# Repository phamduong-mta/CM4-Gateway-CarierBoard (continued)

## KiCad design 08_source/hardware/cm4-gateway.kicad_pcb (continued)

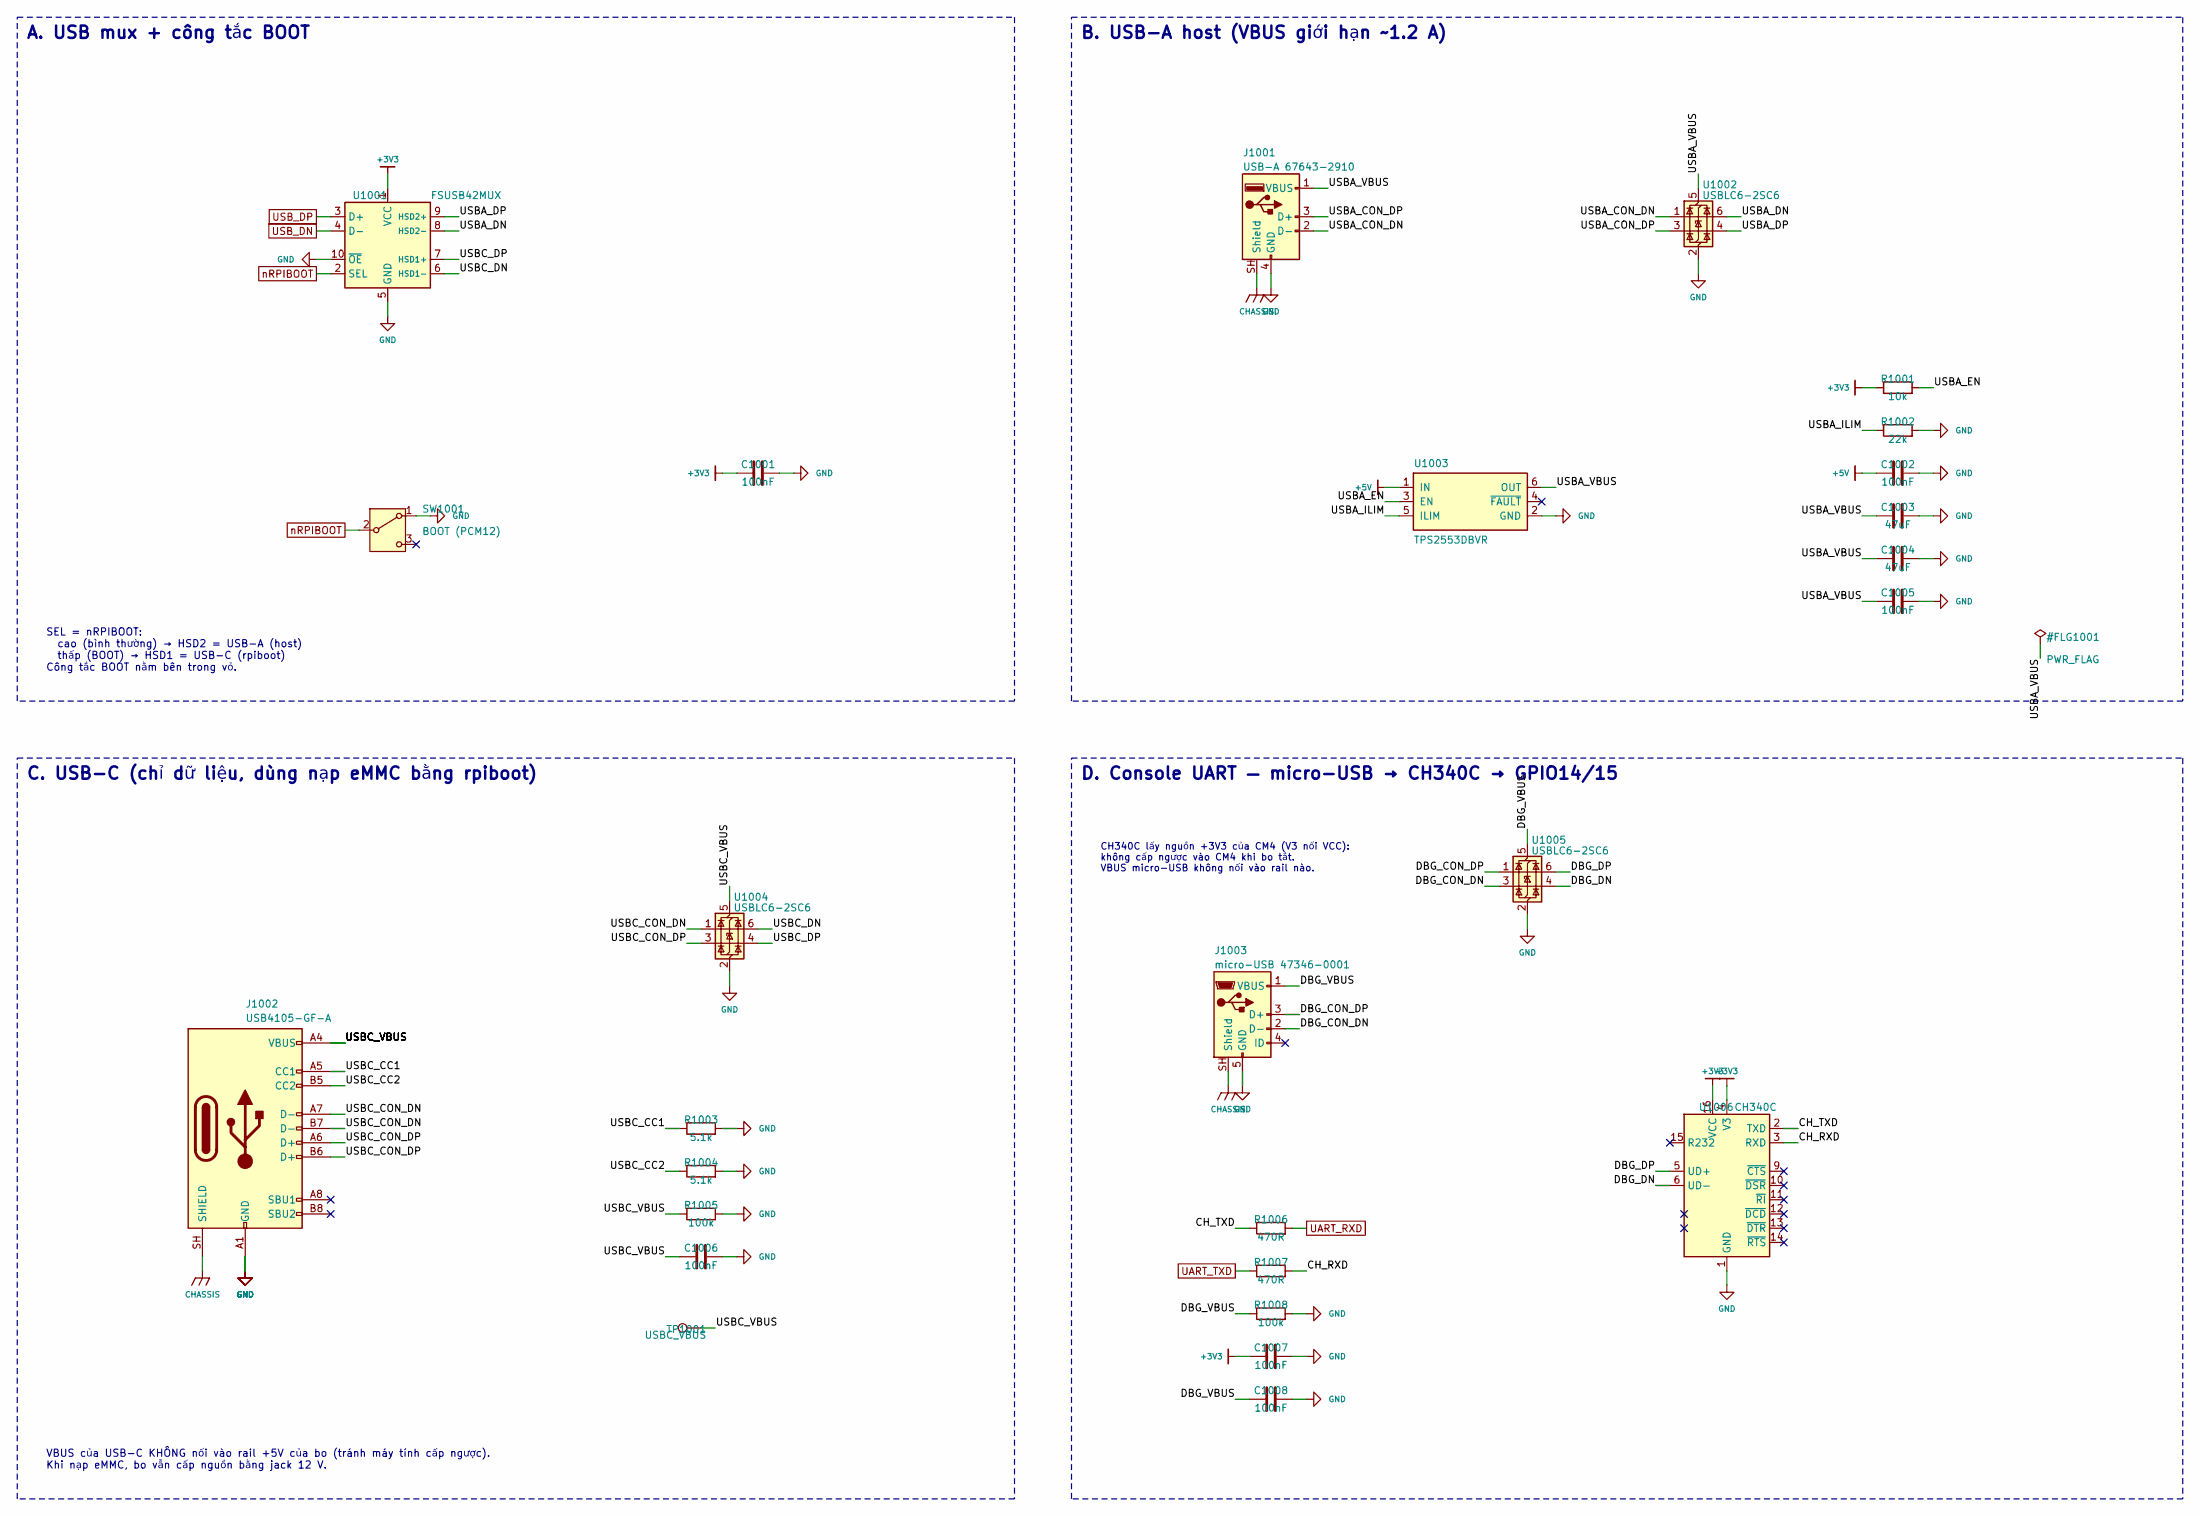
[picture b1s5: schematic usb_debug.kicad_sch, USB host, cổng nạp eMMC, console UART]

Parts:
C1001, C1002, C1005, C1006, C1007, C1008: 100nF; C_0402_1005Metric; MPN CL05B104KO5NNNC; LCSC C1525
C1003, C1004: 47uF; C_1206_3216Metric; MPN CL31A476MPHNNNE; LCSC C96123
J1001: USB-A 67643-2910; USB_A_Molex_67643_Horizontal; MPN 67643-2910; LCSC C564920
J1002: USB4105-GF-A; USB_C_Receptacle_GCT_USB4105-xx-A_16P_TopMnt_Horizontal; MPN USB4105-GF-A; LCSC C3020560
J1003: micro-USB 47346-0001; USB_Micro-B_Molex_47346-0001; MPN 47346-0001; LCSC C132560
R1001: 10k; R_0402_1005Metric; MPN 0402WGF1002TCE; LCSC C25744
R1002: 22k; R_0402_1005Metric; MPN 0402WGF2202TCE; LCSC C25768
R1003, R1004: 5.1k; R_0402_1005Metric; MPN 0402WGF5101TCE; LCSC C25905
R1005, R1008: 100k; R_0402_1005Metric; MPN 0402WGF1003TCE; LCSC C25741
R1006, R1007: 470R; R_0402_1005Metric; MPN 0402WGF4700TCE; LCSC C25117
SW1001: BOOT (PCM12); SW_SPDT_PCM12; MPN PCM12SMTR; LCSC C221841
TP1001: USBC_VBUS; TestPoint_Pad_D1.0mm
U1001: FSUSB42MUX; MSOP-10_3x3mm_P0.5mm; MPN FSUSB42MUX; LCSC C11355
U1002, U1004, U1005: USBLC6-2SC6; SOT-23-6; MPN USBLC6-2SC6; LCSC C7519
U1003: TPS2553DBVR; SOT-23-6; MPN TPS2553DBVR; LCSC C55266
U1006: CH340C; SOIC-16_3.9x9.9mm_P1.27mm; MPN CH340C; LCSC C84681

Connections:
+3V3: C1001.1, C1007.1, R1001.1, U1001.1 (VCC), U1006.4 (V3), U1006.16 (VCC); also elsewhere on the board
+5V: C1002.1, U1003.1 (IN); also elsewhere on the board
/USB_Debug/CH_RXD: R1007.2, U1006.3 (RXD)
/USB_Debug/CH_TXD: R1006.1, U1006.2 (TXD)
/USB_Debug/DBG_CON_DN: J1003.2 (D-), U1005.3 (I/O2)
/USB_Debug/DBG_CON_DP: J1003.3 (D+), U1005.1 (I/O1)
/USB_Debug/DBG_DN: U1005.4 (I/O2), U1006.6 (UD-)
/USB_Debug/DBG_DP: U1005.6 (I/O1), U1006.5 (UD+)
/USB_Debug/DBG_VBUS: C1008.1, J1003.1 (VBUS), R1008.1, U1005.5 (VBUS)
/USB_Debug/USBA_CON_DN: J1001.2 (D-), U1002.1 (I/O1)
/USB_Debug/USBA_CON_DP: J1001.3 (D+), U1002.3 (I/O2)
/USB_Debug/USBA_DN: U1001.8 (HSD2-), U1002.6 (I/O1)
/USB_Debug/USBA_DP: U1001.9 (HSD2+), U1002.4 (I/O2)
/USB_Debug/USBA_EN: R1001.2, U1003.3 (EN)
/USB_Debug/USBA_ILIM: R1002.1, U1003.5 (ILIM)
/USB_Debug/USBA_VBUS: C1003.1, C1004.1, C1005.1, J1001.1 (VBUS), U1002.5 (VBUS), U1003.6 (OUT)
/USB_Debug/USBC_CC1: J1002.A5 (CC1), R1003.1
/USB_Debug/USBC_CC2: J1002.B5 (CC2), R1004.1
/USB_Debug/USBC_CON_DN: J1002.A7 (D-), J1002.B7 (D-), U1004.1 (I/O1)
/USB_Debug/USBC_CON_DP: J1002.A6 (D+), J1002.B6 (D+), U1004.3 (I/O2)
/USB_Debug/USBC_DN: U1001.6 (HSD1-), U1004.6 (I/O1)
/USB_Debug/USBC_DP: U1001.7 (HSD1+), U1004.4 (I/O2)
/USB_Debug/USBC_VBUS: C1006.1, J1002.A4 (VBUS), J1002.A9 (VBUS), J1002.B4 (VBUS), J1002.B9 (VBUS), R1005.1, TP1001.1, U1004.5 (VBUS)
CHASSIS: J1001.SH (Shield), J1002.SH (SHIELD), J1003.SH (Shield); also elsewhere on the board
GND: C1001.2, C1002.2, C1003.2, C1004.2, C1005.2, C1006.2, C1007.2, C1008.2, J1001.4 (GND), J1002.A1 (GND), J1002.A12 (GND), J1002.B1 (GND), J1002.B12 (GND), J1003.5 (GND), R1002.2, R1003.2, R1004.2, R1005.2, R1008.2, SW1001.1 (A), U1001.5 (GND), U1001.10 (~OE), U1002.2 (GND), U1003.2 (GND), U1004.2 (GND), U1005.2 (GND), U1006.1 (GND); also elsewhere on the board
UART_RXD: R1006.2; also elsewhere on the board
UART_TXD: R1007.1; also elsewhere on the board
USB_DN: U1001.4 (D-); also elsewhere on the board
USB_DP: U1001.3 (D+); also elsewhere on the board
nRPIBOOT: SW1001.2 (B), U1001.2 (SEL); also elsewhere on the board

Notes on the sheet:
A. USB mux + công tắc BOOT
SEL = nRPIBOOT: cao (bình thường) → HSD2 = USB-A (host) thấp (BOOT) → HSD1 = USB-C (rpiboot) Công tắc BOOT nằm bên trong vỏ.
B. USB-A host (VBUS giới hạn ~1.2 A)
C. USB-C (chỉ dữ liệu, dùng nạp eMMC bằng rpiboot)
VBUS của USB-C KHÔNG nối vào rail +5V của bo (tránh máy tính cấp ngược). Khi nạp eMMC, bo vẫn cấp nguồn bằng jack 12 V.
D. Console UART — micro-USB → CH340C → GPIO14/15
CH340C lấy nguồn +3V3 của CM4 (V3 nối VCC): không cấp ngược vào CM4 khi bo tắt. VBUS micro-USB không nối vào rail nào.

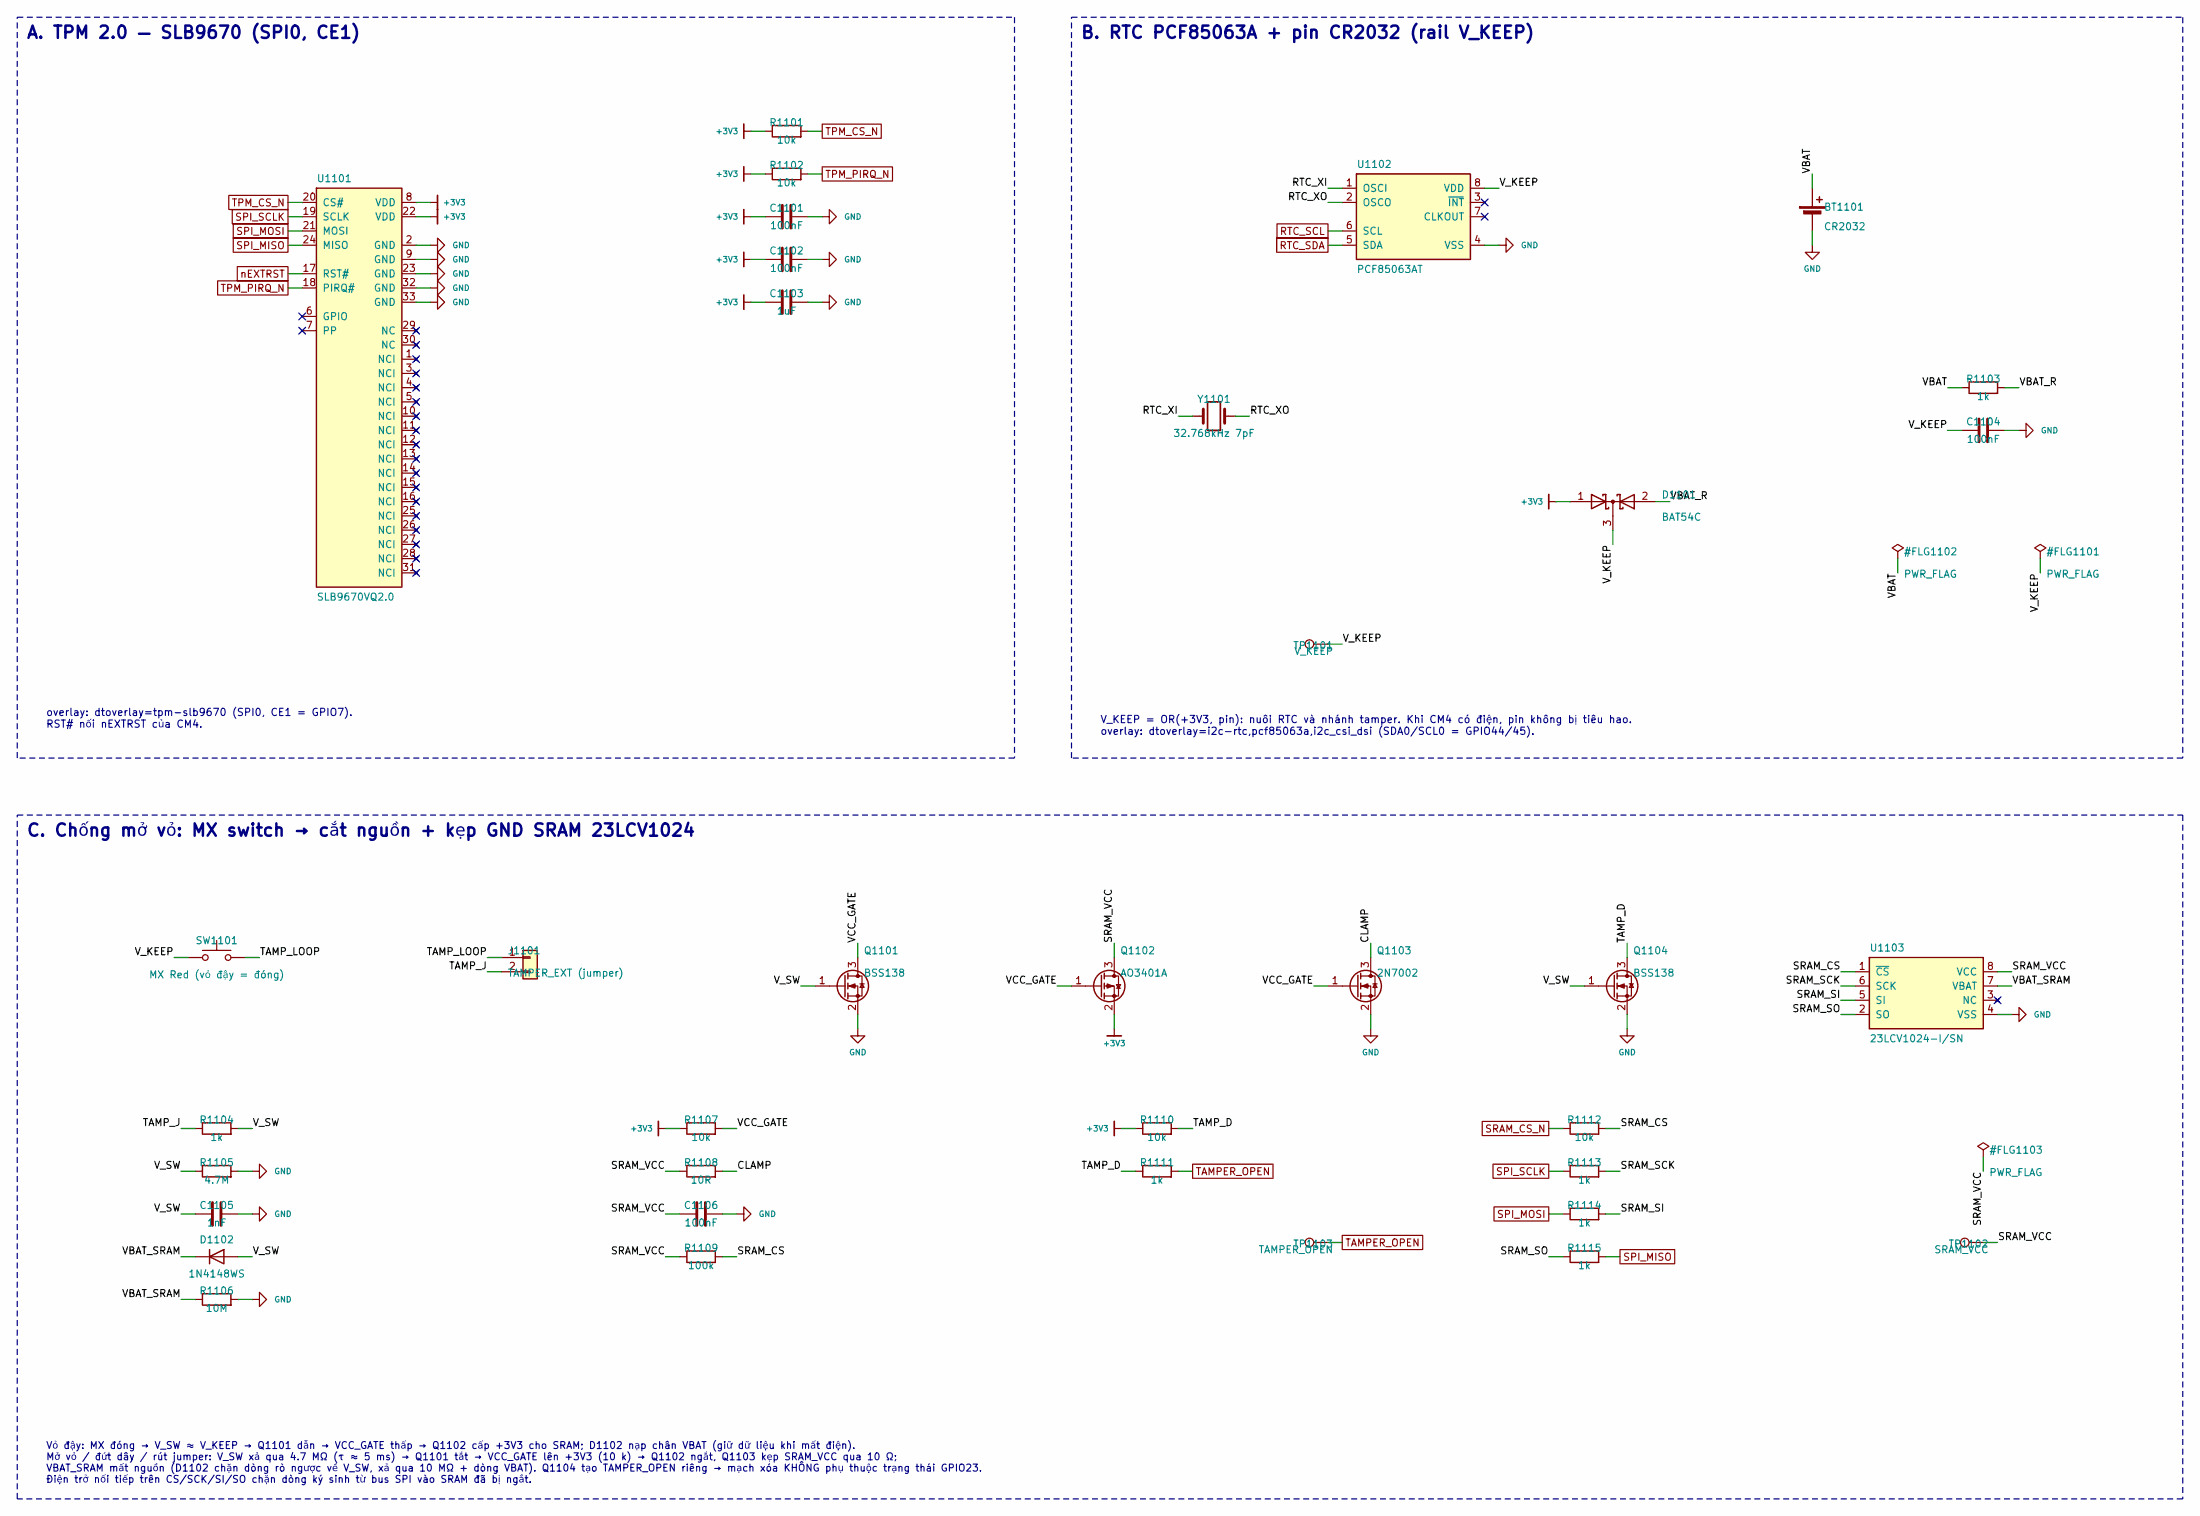
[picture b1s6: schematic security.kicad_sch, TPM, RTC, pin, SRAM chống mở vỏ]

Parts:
BT1101: CR2032; BatteryHolder_Keystone_3034_1x20mm; MPN 3034; LCSC C5199422
C1101, C1102, C1104, C1106: 100nF; C_0402_1005Metric; MPN CL05B104KO5NNNC; LCSC C1525
C1103: 1uF; C_0402_1005Metric; MPN CL05A105KA5NQNC; LCSC C52923
C1105: 1nF; C_0402_1005Metric; MPN CL05B102KB5NNNC; LCSC C14442
D1101: BAT54C; SOT-23; MPN BAT54C; LCSC C2135
D1102: 1N4148WS; D_SOD-323; MPN 1N4148WS; LCSC C2128
J1101: TAMPER_EXT (jumper); PinHeader_1x02_P2.54mm_Vertical; MPN B-2100S02P-A110; LCSC C124375
Q1101, Q1104: BSS138; SOT-23; MPN LBSS138LT1G; LCSC C8490
Q1102: AO3401A; SOT-23; MPN AO3401A; LCSC C15127
Q1103: 2N7002; SOT-23; MPN 2N7002; LCSC C8545
R1101, R1102, R1107, R1110, R1112: 10k; R_0402_1005Metric; MPN 0402WGF1002TCE; LCSC C25744
R1103, R1104, R1111, R1113, R1114, R1115: 1k; R_0402_1005Metric; MPN 0402WGF1001TCE; LCSC C11702
R1105: 4.7M; R_0402_1005Metric; MPN 0402WGF4704TCE; LCSC C474132
R1106: 10M; R_0402_1005Metric; MPN 0402WGF1005TCE; LCSC C26082
R1108: 10R; R_0402_1005Metric; MPN 0402WGF100JTCE; LCSC C25077
R1109: 100k; R_0402_1005Metric; MPN 0402WGF1003TCE; LCSC C25741
SW1101: MX Red (vỏ đậy = đóng); SW_Cherry_MX_1.00u_PCB; MPN CPG151101D05; LCSC C49234236
TP1101: V_KEEP; TestPoint_Pad_D1.0mm
TP1102: SRAM_VCC; TestPoint_Pad_D1.0mm
TP1103: TAMPER_OPEN; TestPoint_Pad_D1.0mm
U1101: SLB9670VQ2.0; QFN-32-1EP_5x5mm_P0.5mm_EP3.6x3.6mm; MPN SLB9670VQ20FW785XTMA1; LCSC C1012863
U1102: PCF85063AT; SOIC-8_3.9x4.9mm_P1.27mm; MPN PCF85063AT/AY; LCSC C5151540
U1103: 23LCV1024-I/SN; SOIC-8_3.9x4.9mm_P1.27mm; MPN 23LCV1024-I/SN; LCSC C615097
Y1101: 32.768kHz 7pF; Crystal_SMD_3215-2Pin_3.2x1.5mm; MPN SC-32S 32.768kHz 7pF; LCSC C97604

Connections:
+3V3: C1101.1, C1102.1, C1103.1, D1101.1 (A), Q1102.2 (S), R1101.1, R1102.1, R1107.1, R1110.1, U1101.8 (VDD), U1101.22 (VDD); also elsewhere on the board
/Security/CLAMP: Q1103.3 (D), R1108.2
/Security/RTC_XI: U1102.1 (OSCI), Y1101.1
/Security/RTC_XO: U1102.2 (OSCO), Y1101.2
/Security/SRAM_CS: R1109.2, R1112.2, U1103.1 (~CS)
/Security/SRAM_SCK: R1113.2, U1103.6 (SCK)
/Security/SRAM_SI: R1114.2, U1103.5 (SI)
/Security/SRAM_SO: R1115.1, U1103.2 (SO)
/Security/SRAM_VCC: C1106.1, Q1102.3 (D), R1108.1, R1109.1, TP1102.1, U1103.8 (VCC)
/Security/TAMP_D: Q1104.3 (D), R1110.2, R1111.1
/Security/TAMP_J: J1101.2, R1104.1
/Security/TAMP_LOOP: J1101.1, SW1101.2
/Security/VBAT: BT1101.1 (+), R1103.1
/Security/VBAT_R: D1101.2 (A), R1103.2
/Security/VBAT_SRAM: D1102.1 (K), R1106.1, U1103.7 (VBAT)
/Security/VCC_GATE: Q1101.3 (D), Q1102.1 (G), Q1103.1 (G), R1107.2
/Security/V_KEEP: C1104.1, D1101.3 (K), SW1101.1, TP1101.1, U1102.8 (VDD)
/Security/V_SW: C1105.1, D1102.2 (A), Q1101.1 (G), Q1104.1 (G), R1104.2, R1105.1
GND: BT1101.2 (-), C1101.2, C1102.2, C1103.2, C1104.2, C1105.2, C1106.2, Q1101.2 (S), Q1103.2 (S), Q1104.2 (S), R1105.2, R1106.2, U1101.2 (GND), U1101.9 (GND), U1101.23 (GND), U1101.32 (GND), U1101.33 (GND), U1102.4 (VSS), U1103.4 (VSS); also elsewhere on the board
RTC_SCL: U1102.6 (SCL); also elsewhere on the board
RTC_SDA: U1102.5 (SDA); also elsewhere on the board
SPI_MISO: R1115.2, U1101.24 (MISO); also elsewhere on the board
SPI_MOSI: R1114.1, U1101.21 (MOSI); also elsewhere on the board
SPI_SCLK: R1113.1, U1101.19 (SCLK); also elsewhere on the board
SRAM_CS_N: R1112.1; also elsewhere on the board
TAMPER_OPEN: R1111.2, TP1103.1; also elsewhere on the board
TPM_CS_N: R1101.2, U1101.20 (CS#); also elsewhere on the board
TPM_PIRQ_N: R1102.2, U1101.18 (PIRQ#); also elsewhere on the board
nEXTRST: U1101.17 (RST#); also elsewhere on the board

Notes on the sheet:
A. TPM 2.0 — SLB9670 (SPI0, CE1)
overlay: dtoverlay=tpm-slb9670 (SPI0, CE1 = GPIO7). RST# nối nEXTRST của CM4.
B. RTC PCF85063A + pin CR2032 (rail V_KEEP)
V_KEEP = OR(+3V3, pin): nuôi RTC và nhánh tamper. Khi CM4 có điện, pin không bị tiêu hao. overlay: dtoverlay=i2c-rtc,pcf85063a,i2c_csi_dsi (SDA0/SCL0 = GPIO44/45).
C. Chống mở vỏ: MX switch → cắt nguồn + kẹp GND SRAM 23LCV1024
Vỏ đậy: MX đóng → V_SW ≈ V_KEEP → Q1101 dẫn → VCC_GATE thấp → Q1102 cấp +3V3 cho SRAM; D1102 nạp chân VBAT (giữ dữ liệu khi mất điện). Mở vỏ / đứt dây / rút jumper: V_SW xả qua 4.7 MΩ (τ ≈ 5 ms) → Q1101 tắt → VCC_GATE lên +3V3 (10 k) → Q1102 ngắt, Q1103 kẹp SRAM_VCC qua 10 Ω; VBAT_SRAM mất nguồn (D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
